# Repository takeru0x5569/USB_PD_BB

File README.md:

# USB_PD_BB
USB PD adapter for bread board

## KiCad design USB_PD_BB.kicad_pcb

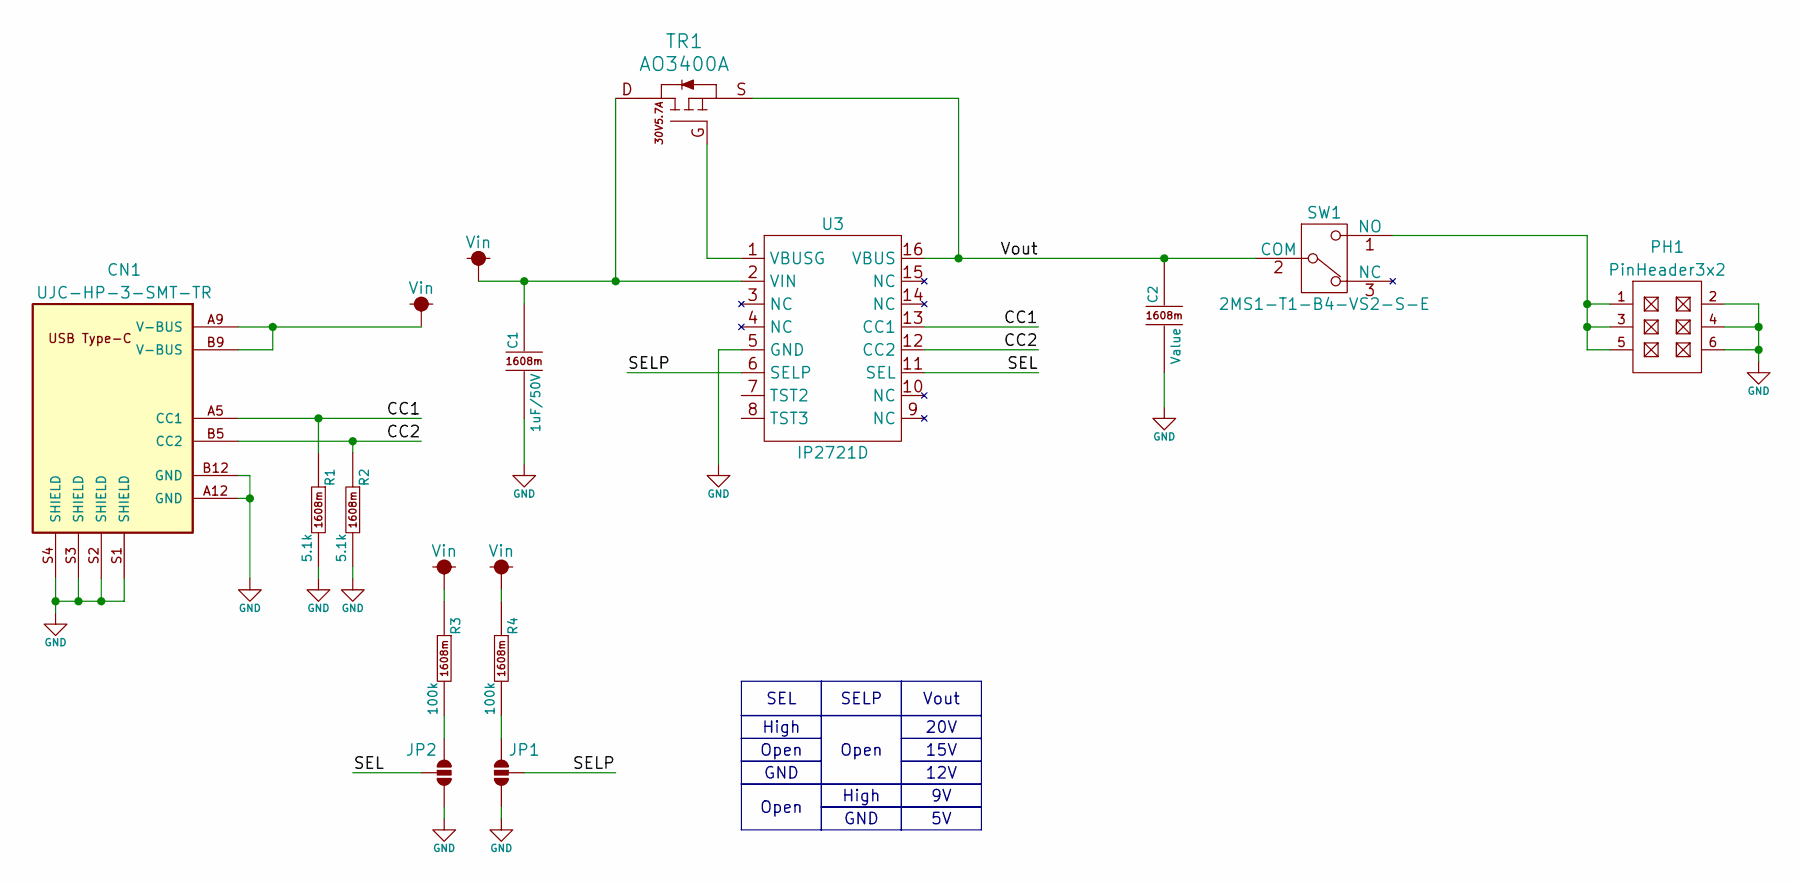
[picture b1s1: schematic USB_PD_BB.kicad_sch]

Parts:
C1: 1uF/50V; CAP1608m
C2: Value; CAP1608m
CN1: UJC-HP-3-SMT-TR
JP1, JP2: SolderJumperSel
PH1: PinHeader3x2
R1, R2: 5.1k; REG1608m
R3, R4: 100k; REG1608m
SW1: 2MS1-T1-B4-VS2-S-E; 2MS1-T1-B4-VS2-Q-E-S
TR1: AO3400A
U3: IP2721D

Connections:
/CC1: CN1.A5 (CC1), R1.1, U3.13 (CC1)
/CC2: CN1.B5 (CC2), R2.1, U3.12 (CC2)
/SEL: JP2.1, U3.11 (SEL)
/SELP: JP1.1, U3.6 (SELP)
/Vout: C2.1, SW1.2 (COM), TR1.S, U3.16 (VBUS)
GND: C1.2, C2.2, CN1.A12 (GND), CN1.B12 (GND), CN1.S1 (SHIELD), CN1.S2 (SHIELD), CN1.S3 (SHIELD), CN1.S4 (SHIELD), JP1.3, JP2.3, PH1.2, PH1.4, PH1.6, R1.2, R2.2, U3.5 (GND)
unnamed: JP1.2, R4.2
unnamed: JP2.2, R3.2
unnamed: PH1.1, PH1.3, PH1.5
unnamed: TR1.G, U3.1 (VBUSG)
Vin: C1.1, CN1.A9 (V-BUS), CN1.B9 (V-BUS), R3.1, R4.1, TR1.D, U3.2 (VIN)

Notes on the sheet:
15V
GND
Open
High
SEL
20V
12V
Vout
SELP

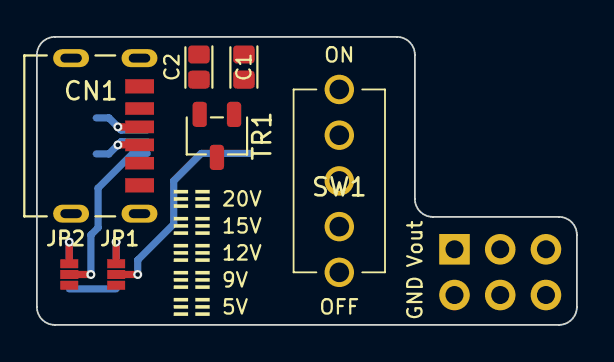
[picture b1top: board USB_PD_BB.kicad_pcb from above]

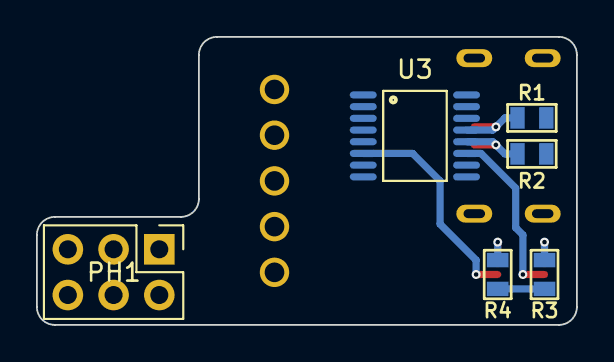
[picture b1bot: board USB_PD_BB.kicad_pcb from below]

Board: 2 copper layers, 30.0 x 16.0 mm, 13 parts (6 on the bottom side), 11 nets.

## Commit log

2023-03-31 add USB-PD
2023-04-02 remove backup files
2023-04-02 add FET ans Switch
2023-04-03 rough artwork.
2023-04-14 add swtich 3D model
